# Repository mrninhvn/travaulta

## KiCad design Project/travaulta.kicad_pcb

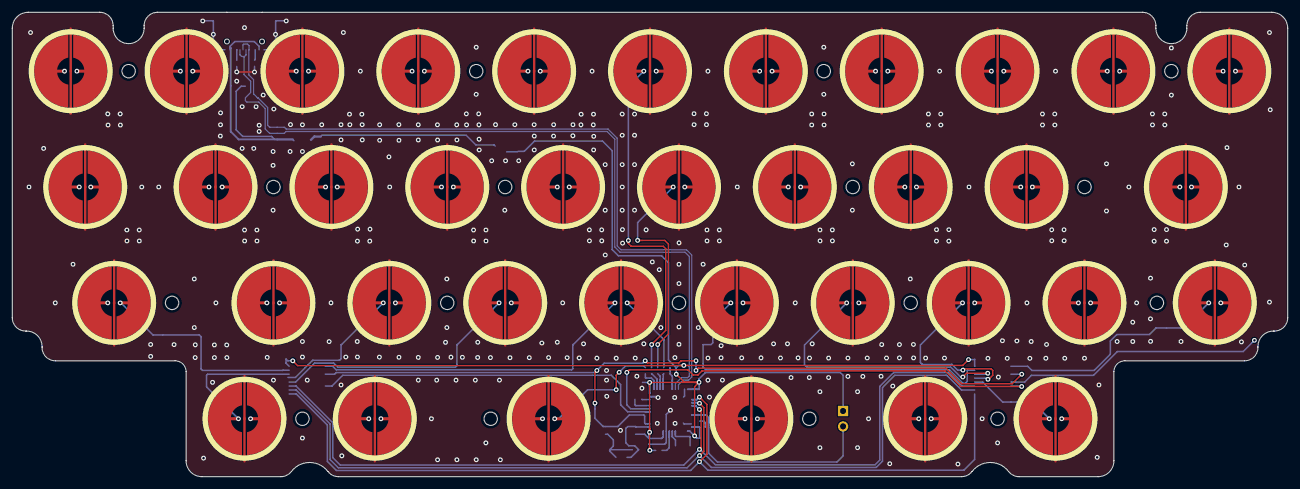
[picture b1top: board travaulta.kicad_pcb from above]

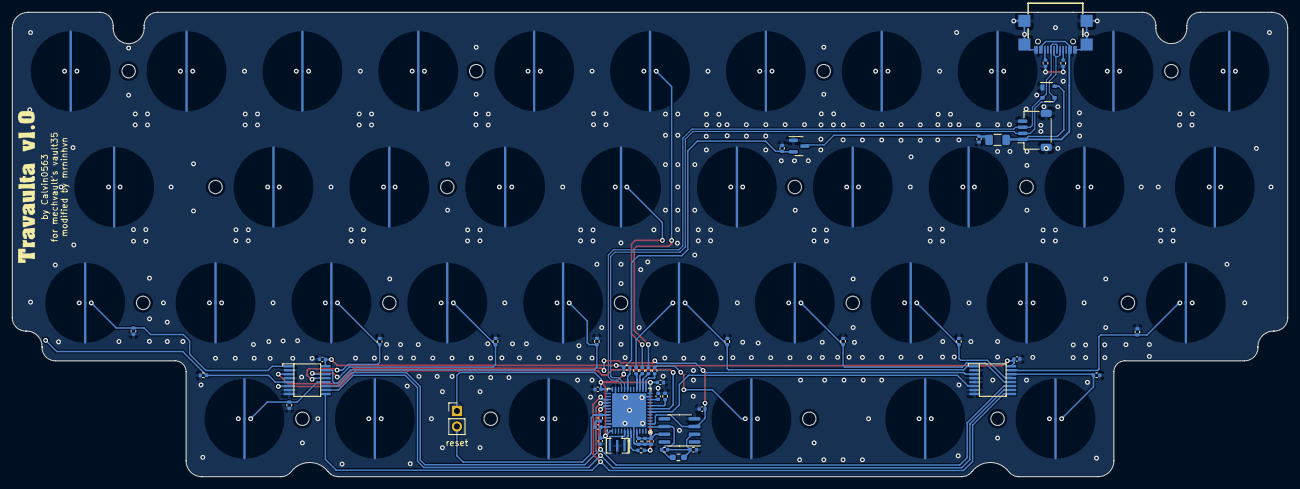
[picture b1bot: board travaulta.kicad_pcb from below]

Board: 4 copper layers, 209.7 x 76.4 mm, 102 parts (48 on the bottom side), 42 nets.

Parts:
C1: 4.7u; C_0402_1005Metric
C4, C5, C11: 1u; C_0402_1005Metric
C6, C7, C8, C9, C10, C12, C13, C15: 100n; C_0402_1005Metric
C14: 220p; C_0402_1005Metric
D1: PRTR5V0U2X; SOT-143
F_USBC1: 500mA; Fuse_1206_3216Metric
H1, H2, H3, H4, H5, H6, H7, H8, H9, H10, H11, H12, H13, H14, H15, H16, H17: MountingHole; HOLE_M2
J1: Conn_01x04_MountingPin; JST_SH_SM04B-SRSS-TB_1x04-1MP_P1.00mm_Horizontal
JP1: Ext_Res; R_0603_1608Metric_Pad0.98x0.95mm_HandSolder
R1, R2, R8, R9: 100; R_0402_1005Metric
R3, R6, R7: 10k; R_0402_1005Metric
R4, R5, R10, R11, R12, R13, R14, R15, R16, R17, R19, R20, R21: 100k; R_0402_1005Metric
R18, R24: 5.1k; R_0402_1005Metric
R23: 1k; R_0402_1005Metric
SW1, SW2, SW3, SW4, SW5, SW6, SW7, SW8, SW9, SW10, SW11, SW12, SW13, SW14, SW15, SW16, SW17, SW18, SW19, SW20, SW21, SW22, SW23, SW24, SW25, SW26, SW27, SW28, SW29, SW30, SW31, SW32, SW33, SW34, SW35, SW36, SW37: EC_SW; ecs_pad_1U_no_ring
SW38: BOOT0; PinHeader_1x02_P2.54mm_Vertical
U1: STM32F401CBUx; QFN-48-1EP_7x7mm_P0.5mm_EP5.6x5.6mm
U2: XC6206PxxxMR; SOT-23
U3, U4: 74HC4051; TSSOP16
U5: OPA350; SOIC-8_3.9x4.9mm_P1.27mm
USB1: TYPEC-304YSSW-ACP16
Y1: 8 MHz; Resonator_SMD_Murata_CSTxExxV-3Pin_3.0x1.1mm

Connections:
+5V: C4.1, F_USBC1.2, U2.3 (VI)
ADC: JP1.1 (A), R21.2, U1.13 (PA3), U5.6 (OUT)
AMUX_SEL_0: U1.41 (PB5), U3.11 (S0), U4.11 (S0)
AMUX_SEL_1: U1.40 (PB4), U3.10 (S1), U4.10 (S1)
AMUX_SEL_2: U1.39 (PB3), U3.9 (S2), U4.9 (S2)
APLEX_EN_PIN_0: U1.18 (PB0), U4.6 (~E)
APLEX_EN_PIN_1: U1.19 (PB1), U3.6 (~E)
APLEX_OUT_PIN_0: C14.2, U1.14 (PA4), U3.3 (A), U4.3 (A), U5.3 (IN+)
BOOT0: R3.1, SW38.2 (B), U1.44 (BOOT0)
BOOT1: R7.2, U1.20 (PB2)
COL0: R15.1, SW1.2, SW12.2, SW22.2, U4.15 (A2)
COL1: R13.1, SW2.2, SW13.2, SW23.2, SW32.2, U4.14 (A1)
COL2: R11.1, SW3.2, SW14.2, SW24.2, SW33.2, U4.13 (A0)
COL3: R17.1, SW4.2, SW15.2, SW25.2, SW34.2, U4.12 (A3)
COL4: R19.1, SW5.2, SW16.2, SW26.2, U4.1 (A4)
COL5: R12.1, SW6.2, SW17.2, SW27.2, SW35.2, U3.15 (A2)
COL6: R10.1, SW7.2, SW18.2, SW28.2, U3.14 (A1)
COL7: R20.1, SW8.2, SW19.2, SW29.2, SW36.2, U3.13 (A0)
COL8: R14.1, SW9.2, SW20.2, SW30.2, SW37.2, U3.12 (A3)
COL9: R16.1, SW10.2, SW21.2, SW31.2, U3.1 (A4)
COL10: R5.1, SW11.2, U3.5 (A5)
D+: D1.2 (I/O1), J1.3, U1.33 (PA12), USB1.6 (DP1), USB1.8 (DP2)
D-: D1.3 (I/O2), J1.2, U1.32 (PA11), USB1.5 (DN2), USB1.7 (DN1)
GND: C1.2, C4.2, C5.2, C6.2, C7.2, C8.2, C9.2, C10.2, C11.2, C12.2, C13.2, C14.1, C15.2, D1.1 (GND), J1.4, J1.MP (MountPin), R3.2, R5.2, R7.1, R10.2, R11.2, R12.2, R13.2, R14.2, R15.2, R16.2, R17.2, R18.1, R19.2, R20.2, R23.2, R24.2, SW1.3 (SG), SW2.3 (SG), SW3.3 (SG), SW4.3 (SG), SW5.3 (SG), SW6.3 (SG), SW7.3 (SG), SW8.3 (SG), SW9.3 (SG), SW10.3 (SG), SW11.3 (SG), SW12.3 (SG), SW13.3 (SG), SW14.3 (SG), SW15.3 (SG), SW16.3 (SG), SW17.3 (SG), SW18.3 (SG), SW19.3 (SG), SW20.3 (SG), SW21.3 (SG), SW22.3 (SG), SW23.3 (SG), SW24.3 (SG), SW25.3 (SG), SW26.3 (SG), SW27.3 (SG), SW28.3 (SG), SW29.3 (SG), SW30.3 (SG), SW31.3 (SG), SW32.3 (SG), SW33.3 (SG), SW34.3 (SG), SW35.3 (SG), SW36.3 (SG), SW37.3 (SG), U1.8 (VSSA), U1.23 (VSS), U1.35 (VSS), U1.47 (VSS), U1.49 (VSS), U2.1 (GND), U3.2 (A6), U3.4 (A7), U3.7 (VEE), U3.8 (GND), U4.2 (A6), U4.4 (A7), U4.5 (A5), U4.7 (VEE), U4.8 (GND), U5.4 (V-), USB1.1 (GND), USB1.12 (GND), USB1.13 (SHIELD), Y1.2
NRST: R6.2, U1.7 (NRST)
unnamed: JP1.2 (B), R21.1, R23.1, U5.2 (IN-)
unnamed: R4.1, U1.31 (PA10)
unnamed: R1.1, U1.25 (PB12)
unnamed: R9.1, U1.26 (PB13)
unnamed: R8.2, U1.27 (PB14)
unnamed: R2.2, U1.28 (PB15)
unnamed: C1.1, U1.22 (VCAP1)
unnamed: R18.2, USB1.4 (CC1)
unnamed: R24.1, USB1.10 (CC2)
ROW0: R9.2, SW1.1, SW2.1, SW3.1, SW4.1, SW5.1, SW6.1, SW7.1, SW8.1, SW9.1, SW10.1, SW11.1
ROW1: R8.1, SW12.1, SW13.1, SW14.1, SW15.1, SW16.1, SW17.1, SW18.1, SW19.1, SW20.1, SW21.1
ROW2: R2.1, SW22.1, SW23.1, SW24.1, SW25.1, SW26.1, SW27.1, SW28.1, SW29.1, SW30.1, SW31.1
ROW3: R1.2, SW32.1, SW33.1, SW34.1, SW35.1, SW36.1, SW37.1
VBAT: C5.1, C6.1, C7.1, C8.1, C9.1, C10.1, C11.1, C12.1, C13.1, C15.1, R4.2, R6.1, SW38.1 (A), U1.1 (VBAT), U1.9 (VREF+), U1.24 (VDD), U1.36 (VDD), U1.48 (VDD), U2.2 (VO), U3.16 (VCC), U4.16 (VCC), U5.7 (V+)
VCC: D1.4 (VCC), F_USBC1.1, J1.1, USB1.2 (VBUS), USB1.11 (VBUS)
XTAL0: U1.5 (PH0), Y1.3
XTAL1: U1.6 (PH1), Y1.1

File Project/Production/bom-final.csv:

Designator,Footprint,Quantity,Value,LCSC Part #
C1,0402,1,4.7u,C23733
"C10, C12, C13, C15, C6, C7, C8, C9",0402,8,100n,C307331
"C11, C4, C5",0402,3,1u,C52923
C14,0402,1,220p,C1530
D1,SOT-143,1,PRTR5V0U2X,C2827688
F_USBC1,1206,1,500mA,C70076
J1,JST_SH_SM04B-SRSS-TB_1x04-1MP_P1.00mm_Horizontal,1,Conn_01x04_MountingPin,C160404
"R1, R2, R8, R9",0402,4,100,C25076
"R10, R11, R12, R13, R14, R15, R16, R17, R19, R20, R21, R5",0402,12,100k,C25741
"R18, R24",0402,2,5.1k,C25905
R23,0402,1,1k,C11702
"R3, R6",0402,2,10k,C25744
R4,0402,1,100k,C25741
R7,0402,1,10k,C25744
U1,QFN-48-1EP_7x7mm_P0.5mm_EP5.6x5.6mm,1,STM32F401CBUx,C118825
U2,SOT-23,1,XC6206PxxxMR,C5446
"U3, U4",TSSOP16,2,74HC4051,C5645
U5,SOIC-8_3.9x4.9mm_P1.27mm,1,OPA350,C13388
USB1,TYPEC-304YSSW-ACP16,1,TYPEC-304YSSW-ACP16,C2840392
Y1,Resonator_SMD_Murata_CSTxExxV-3Pin_3.0x1.1mm,1,8 MHz,C907975

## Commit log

2025-02-10 add daughterboard header
2025-02-11 fix solder paste
2025-06-11 add bom html
2025-06-11 jlcpcb bom
